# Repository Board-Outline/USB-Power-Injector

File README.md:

# USB Power Injector

The USB Power Injector allows a convenient way to power up USB 2.0 devices from a lab power supply, while still allowing data transfer from the device to the host. 

## The problem

When powering devices from a standard USB 2.0 port, either from a PC or from a standard USB hub, you never have the niceties that an adjustable lab style power supply has. 
During development that means you can’t set precise voltage and current limits. In the best case scenario, that means you can’t test under/over voltage protections. 
In the worst case, you run excessive current trough your device and you don’t even know that’s happened.
USB hubs tend to have overcurrent protection, but most don’t send the overcurrent event to the operating system. 
That can cause confusion and loss of time for a hardware engineer during development or to testing personnel during production.  

# Open Source Certified

The USB Power Injector is officially certified by the Open Source Hardware Association, with certificate number BG000082.

The project was made using KiCad.

# License

The project is released under the [Creative Commons Attribution-ShareAlike 4.0 International (CC BY-SA 4.0)](https://creativecommons.org/licenses/by-sa/4.0/).

Note: This is a human-readable summary of (and not a substitute for) the [license](https://creativecommons.org/licenses/by-sa/4.0/legalcode).

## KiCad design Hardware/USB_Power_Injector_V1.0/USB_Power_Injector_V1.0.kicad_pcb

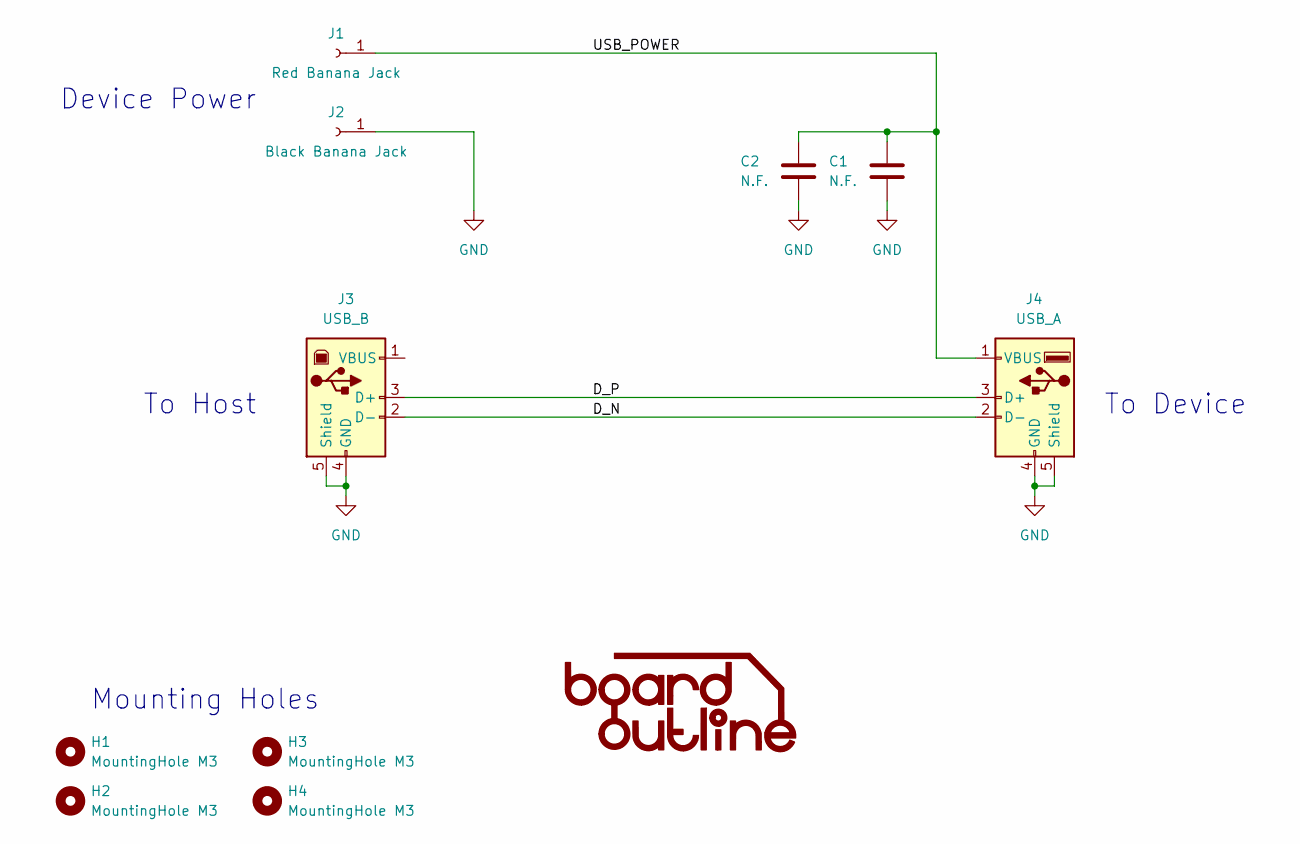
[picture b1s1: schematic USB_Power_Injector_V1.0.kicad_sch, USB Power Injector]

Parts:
C1, C2: N.F.; C_1210_3225Metric_Pad1.33x2.70mm_HandSolder
H1, H2, H3, H4: MountingHole M3; MountingHole_3.2mm_M3_ISO7380
J1: Red Banana Jack; 4mm_Banana_Jack_Red_Deltron_571-0500; Manufacturer Part Number 571-0500
J2: Black Banana Jack; 4mm_Banana_Jack_Black_Deltron_571-0100; Manufacturer Part Number 571-0100
J3: USB_B; USB_B_OST_USB-B1HSxx_Horizontal; Manufacturer Part Number UJ2-BH-1-TH
J4: USB_A; USB_A_CONNFLY_DS1095-WNR0; Manufacturer Part Number SS-52100-001

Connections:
/D_N: J3.2 (D-), J4.2 (D-)
/D_P: J3.3 (D+), J4.3 (D+)
/USB_POWER: C1.1, C2.1, J1.1, J4.1 (VBUS)
GND: C1.2, C2.2, J2.1, J3.4 (GND), J3.5 (Shield), J4.4 (GND), J4.5 (Shield)

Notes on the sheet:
Mounting Holes
To Device
Device Power
To Host

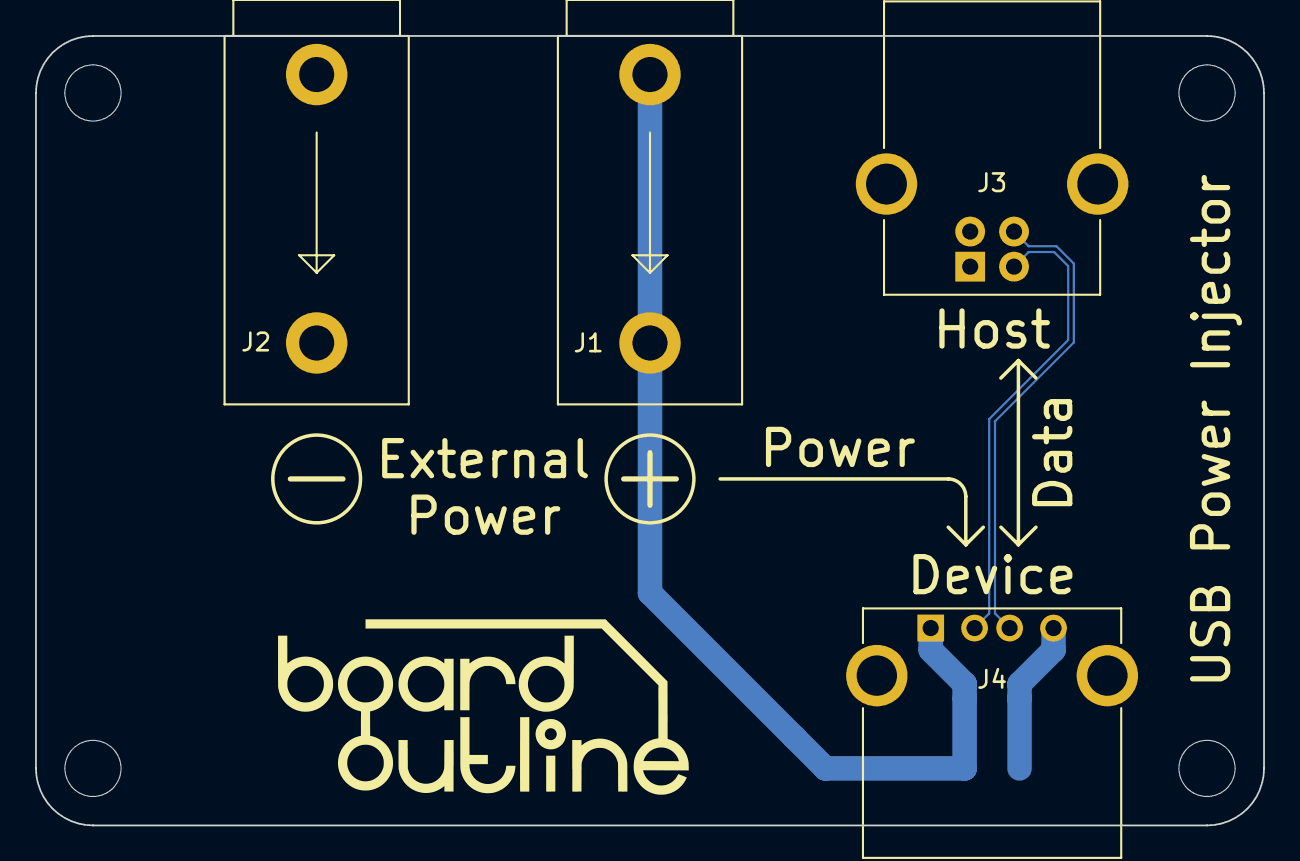
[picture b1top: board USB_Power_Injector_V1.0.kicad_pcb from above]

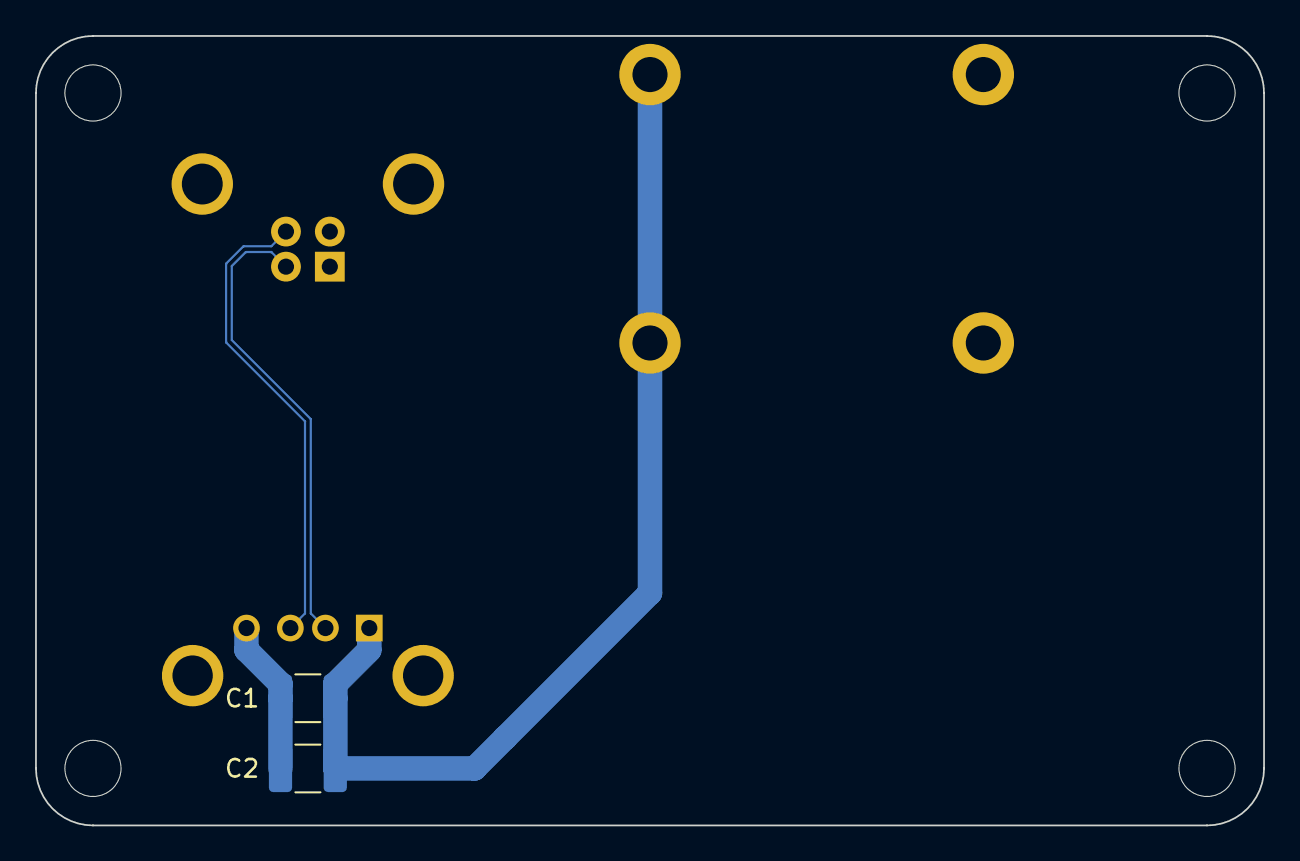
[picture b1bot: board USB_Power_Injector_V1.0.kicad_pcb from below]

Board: 4 copper layers, 70.0 x 45.0 mm, 10 parts (2 on the bottom side), 4 nets.

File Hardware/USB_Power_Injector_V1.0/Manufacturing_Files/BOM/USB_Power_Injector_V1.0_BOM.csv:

"Source:","D:\Board Outline\Repos\USB-Power-Injector\Hardware\USB_Power_Injector_V1.0\USB_Power_Injector_V1.0.kicad_sch"
"Date:","02-Oct-22 17:32:15"
"Tool:","Eeschema (6.0.6)"
"Generator:","C:\Program Files\KiCad\6.0\bin\scripting\plugins/bom_csv_grouped_by_value.py"
"Component Count:","4"

"Individual Components:"

"Item","Qty","Reference(s)","Value","LibPart","Footprint","Datasheet","Manufacturer","Manufacturer Part Number"
"","","J1","Red Banana Jack","Connector:Conn_01x01_Female","USB_Power_Injector:4mm_Banana_Jack_Red_Deltron_571-0500","~","Deltron","571-0500 "
"","","J2","Black Banana Jack","Connector:Conn_01x01_Female","USB_Power_Injector:4mm_Banana_Jack_Black_Deltron_571-0100","~","Deltron","571-0100 "
"","","J3","USB_B","Connector:USB_B","USB_Power_Injector:USB_B_OST_USB-B1HSxx_Horizontal"," ~","CUI Devices","UJ2-BH-1-TH"
"","","J4","USB_A","Connector:USB_A","USB_Power_Injector:USB_A_CONNFLY_DS1095-WNR0"," ~","Stewart Connector / Bel","SS-52100-001"



"Collated Components:"

"Item","Qty","Reference(s)","Value","LibPart","Footprint","Datasheet","Manufacturer","Manufacturer Part Number"
"1","1","J1","Red Banana Jack","Connector:Conn_01x01_Female","USB_Power_Injector:4mm_Banana_Jack_Red_Deltron_571-0500","~","Deltron","571-0500 "
"2","1","J2","Black Banana Jack","Connector:Conn_01x01_Female","USB_Power_Injector:4mm_Banana_Jack_Black_Deltron_571-0100","~","Deltron","571-0100 "
"3","1","J3","USB_B","Connector:USB_B","USB_Power_Injector:USB_B_OST_USB-B1HSxx_Horizontal"," ~","CUI Devices","UJ2-BH-1-TH"
"4","1","J4","USB_A","Connector:USB_A","USB_Power_Injector:USB_A_CONNFLY_DS1095-WNR0"," ~","Stewart Connector / Bel","SS-52100-001"

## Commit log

2022-08-20 Changed readme
2022-08-20 Update LICENSE
2022-08-25 Added Licence_Facts
2022-08-26 Fixed licence and added OSHWA mark
    The licence had software marked on it by mistake. Removed
    Added OSHWA cert.
2022-09-24 BOM changes
    Excluded the mounting holes and N.F. components from BOM generation. BOM generated.
2022-10-02 Added assembly drawing layers
2022-10-02 Fixed gitignore
2023-04-03 Added 2L version of the PCB
